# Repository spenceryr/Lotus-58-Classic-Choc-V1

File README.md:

### Notice! Project files in the development branches are NOT intended for public use in production of PCB's, may or may not be tested and may change or be removed without notice! 
If you order PCB's from these, YOU bear the sole responsibility for how these turn out!!! Please use the Gerber files for producing PCB's, found under the header 'Releases' instead (Look here >>). Also please note the difference between a 'Pre-release' (partially/fully untested, basically what I order a prototype PCB from to test) and a full actual 'Release' which is fully tested, built and ready to be used to produce PCB's.

# Lotus 58 Glow - Classic
#### Lotus 58 Classic is the wired designs of the Lotus keyboard. Wireless with BLE and 2.4Ghz dongled wireless reside in other repositories.

Starting with simple tweaks to the Lily58 Glow before ordering a set of PCB's it quickly spiraled out of control, and I ended up with what wasn't quite a Lily58 anymore, and although very similar in layout, it is no longer compatible with plate and case design. 

Because of this, it was renamed Lotus58, referencing another flower much like the lily in the name Lily58.

(photo from reddit by u/bduzik)

## General Specifications

- Layout very similar to the original Lily58 family
- Per key RGB and RGB underglow
- Kaihl Hot-swap sockets for MX compatible switches
- Can be used as a standalone Gamepad for either hand
- Optional 0.91" OLED Screens and rotary encoders (one each per side)
- All components through-hole and easily soldered for beginners (SMD option for diodes)
- Designed with a sandwich-style plate/case as part of the design

## Layout variations

- Optional plate layout with OLED screen (Encoder can be placed on upper thumb key position)
- Optional plate layout with rotary encoder (Removes OLED screen for that side)  
- Optional plate layout with no hole for OLED or upper encoder (Encoder can be placed on upper thumb key position)

## 3D-printed Cases
**There are a couple of 'official' commissioned designs for 3D printed cases for the Lotus 58 Glow, available in a separate Git [here](https://github.com/TweetyDaBird/Lotus-Cases).** 

And you can find several more made by users using Google, and/or by joining the Discord channel and chatting to the builders/designers and users.

## Things to note when ordering PCB's
### Finding the Gerber files
If you are not aiming at modifying things, don't look for the gerber files in the folders, pretty please!</BR>
And please don't open yet another issue about it! </BR>
The gerber files are where they belong, zipped up in releases, look under that header for the version you want.

### Tips & Tricks
- Most PCB manufacturers have a MOQ of 5 PCB's, meaning you end up with 2½ keyboards when finished.
- The recommended PCB thickness is 1.6 mm, both for the main PCB and plates to allow the keyswitches to grip the plate and lock in place securely.

If ordering from [JLCPCB](https://www.jlcpcb.com) the plate Gerber files include a reference putting the added serial etc on a breakaway part for a clean look with minimal cost, if using another manufacturer it's possible they have additional fee's for removing the extra text, or you should consider plotting the Gerber files yourself with the correct reference for your manufacturer. Otherwise use the standard settings from JLPCB.

## Build guide
**Some basic build instructions are in the [WIKI](https://github.com/TweetyDaBird/Lotus-58-Classic/wiki), and I really try to keep these updated.** But please keep in mind that whenever these instructions conflict with information on the PCB silkscreen, the silkscreen is and always will be the correct source of information! It's always updated with the version, and the most current information for the PCB version in question. 

**The intent has always been that the keyboard should be able to be fully built with some very basic soldering skills and the instructions on the silkscreen.**

### Discord for further build help and discussions!

## Buy a kit!
I sell complete kits, making it easy to build your keyboard, and it also supports prototypes for new wacky ones.

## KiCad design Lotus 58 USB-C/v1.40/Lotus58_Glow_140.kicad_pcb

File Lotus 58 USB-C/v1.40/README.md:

# Lotus 58 v1.40

Starting with simple tweaks to the Lily58 Glow before ordering a set of PCB's it quickly spiraled out of control, and I ended up with what wasn't quite a Lily58 anymore, and although very similar in layout, it is no longer compatible with plate and case design. 

Because of this, it was renamed Lotus58, referencing another flower much like the lily in the name Lily58.

# Lotus 58 Glow

(photo from reddit by u/bduzik)

Fully compatabile with v1.11, physically identical outline for plates etc. and identical Firmware.

# Parts needed

| Name of part | Qty. | Optional | Remarks | Aliexpress |
| ------------ | ---- | -------- | ------- | --------------- |
| PCB          | 2    | X        | 1,6mm thick | X           |
| Top plate         | 2 | X        | Optional layouts for OLED or encoder in top position. | X |
| Bottom plate         | 2 | X        | X | X |
| Kailh hotswap socket | 56-58 | X | Qty. depends on layout. | [link](https://www.aliexpress.com/item/-/4001051840976.html?spm=a2g0s.8937460.0.0.6f132e0eKYB5RQ&_ga=2.174414626.1036705865.1612730332-979734211.1611132916&_gac=1.119713146.1611132916.CjwKCAiAxp-ABhALEiwAXm6IyZF-HtTdP3MQioG5GOxLvsaJfBbhqTGIQbmV0LXKDx2MZSDJJJTbaBoCPkoQAvD_BwE) |
| Diodes 1N4841 (TH) or 1N4148W (SMD) | 56-58 | X | Qty. depends on layout. TH recommended for beginners. | [link(TH)](https://www.aliexpress.com/item/HOT-SELL-100-PCS-1N4148-DO-35-IN4148-Silicon-Switching-Diode-FREE-SHIPPMENT/32660088529.html?spm=a2g0s.8937460.0.0.c1b82e0edjrOT3&_ga=2.216963734.1036705865.1612730332-979734211.1611132916&_gac=1.53192282.1611132916.CjwKCAiAxp-ABhALEiwAXm6IyZF-HtTdP3MQioG5GOxLvsaJfBbhqTGIQbmV0LXKDx2MZSDJJJTbaBoCPkoQAvD_BwE) or [link(SMD)](https://www.aliexpress.ru/item/-/1005002059571417.html?spm=a2g0s.8937460.0.0.c1b82e0edjrOT3&_ga=2.216963734.1036705865.1612730332-979734211.1611132916&_gac=1.53192282.1611132916.CjwKCAiAxp-ABhALEiwAXm6IyZF-HtTdP3MQioG5GOxLvsaJfBbhqTGIQbmV0LXKDx2MZSDJJJTbaBoCPkoQAvD_BwE) |
| Capacitors 100 nF | 0-4 | ✔ | Qty. depends on layout. 2 needed for each encoder installed. | [link](https://www.aliexpress.com/item/-/32971478818.html?spm=a2g0s.8937460.0.0.6f132e0eKYB5RQ&_ga=2.149198518.1036705865.1612730332-979734211.1611132916&_gac=1.48473428.1611132916.CjwKCAiAxp-ABhALEiwAXm6IyZF-HtTdP3MQioG5GOxLvsaJfBbhqTGIQbmV0LXKDx2MZSDJJJTbaBoCPkoQAvD_BwE) |
| 0.91" OLED Display | 0-2 | ✔ | Qty. depends on layout. | [link](https://www.aliexpress.com/item/-/4001028384269.html?spm=a2g0s.8937460.0.0.c1b82e0edjrOT3&_ga=2.241041155.1036705865.1612730332-979734211.1611132916&_gac=1.219449963.1611132916.CjwKCAiAxp-ABhALEiwAXm6IyZF-HtTdP3MQioG5GOxLvsaJfBbhqTGIQbmV0LXKDx2MZSDJJJTbaBoCPkoQAvD_BwE) |
| USB C Connector | 2 | X | X | [link](https://www.lcsc.com/product-detail/USB-Connectors_G-Switch-GT-USB-7014C_C963373.html) |
| SRV05-4	ESD | 2 | X | ESD protection for USB link. | [link](https://www.lcsc.com/product-detail/Electrostatic-and-Surge-Protection-TVS-ESD_TECH-PUBLIC-SRV05-4_C558418.html)|
| Ferrite bead | 4 | X | ESD protection for USB link. | [link](https://www.lcsc.com/product-detail/Ferrite-Beads_Murata-Electronics-BLM18SG700TZ1D_C882974.html) |
| M2 * 10 mm standoff | 10 | X | Rounded, max 3.7 mm in diameter | [link](https://www.aliexpress.com/item/-/32863484622.html?spm=a2g0s.8937460.0.0.c1b82e0edjrOT3&_ga=2.215809815.1036705865.1612730332-979734211.1611132916&_gac=1.26395343.1611132916.CjwKCAiAxp-ABhALEiwAXm6IyZF-HtTdP3MQioG5GOxLvsaJfBbhqTGIQbmV0LXKDx2MZSDJJJTbaBoCPkoQAvD_BwE) |
| M2 * 4 mm screw | 20 | X | 4-8 mm length fits, low profile hex head recommended | [link](https://www.aliexpress.com/item/-/32966917947.html?spm=a2g0s.8937460.0.0.c1b82e0edjrOT3&_ga=2.246923140.1036705865.1612730332-979734211.1611132916&_gac=1.263439230.1611132916.CjwKCAiAxp-ABhALEiwAXm6IyZF-HtTdP3MQioG5GOxLvsaJfBbhqTGIQbmV0LXKDx2MZSDJJJTbaBoCPkoQAvD_BwE) |
| Silicon pads | 10 | X | X | [link](https://www.aliexpress.com/item/-/32912066603.html?spm=a2g0s.8937460.0.0.6f132e0eKYB5RQ&_ga=2.145547188.1036705865.1612730332-979734211.1611132916&_gac=1.57255896.1611132916.CjwKCAiAxp-ABhALEiwAXm6IyZF-HtTdP3MQioG5GOxLvsaJfBbhqTGIQbmV0LXKDx2MZSDJJJTbaBoCPkoQAvD_BwE) |
| Pro Micro | 2 | X | Can be built with various ProMicro clones as well as Elite C (Or nice!nano for a wireless keyboard) | [link](https://www.aliexpress.com/item/-/32849563958.html?spm=a2g0s.8937460.0.0.c1b82e0edjrOT3&_ga=2.175422242.1036705865.1612730332-979734211.1611132916&_gac=1.225165928.1611132916.CjwKCAiAxp-ABhALEiwAXm6IyZF-HtTdP3MQioG5GOxLvsaJfBbhqTGIQbmV0LXKDx2MZSDJJJTbaBoCPkoQAvD_BwE) |
| MillMax low profile sockets | 1 | ✔ | Purchased as 1x64 pin and split | [link](https://eu.mouser.com/ProductDetail/575-641503)|
| Rotary Encoder | 0-2 | ✔ | Qty. depends on layout. | [link](https://www.aliexpress.com/item/10000056483250.html?spm=a2g0o.productlist.0.0.64951c5fKcPiug&algo_pvid=b530d9b1-fbd2-4598-bf53-bece1343826f&algo_expid=b530d9b1-fbd2-4598-bf53-bece1343826f-2&btsid=2100bdd016135510210168102eefcc&ws_ab_test=searchweb0_0,searchweb201602_,searchweb201603_) |
| Rotary Encoder Knob | 0-2 | ✔ | One needed for each encoder. Clearance for max 24 mm diameter, pick halfshaft or spline according to encoder choice.  | [link](https://www.aliexpress.com/item/10000056483250.html?spm=a2g0o.productlist.0.0.64951c5fKcPiug&algo_pvid=b530d9b1-fbd2-4598-bf53-bece1343826f&algo_expid=b530d9b1-fbd2-4598-bf53-bece1343826f-2&btsid=2100bdd016135510210168102eefcc&ws_ab_test=searchweb0_0,searchweb201602_,searchweb201603_) |
| SK6803/SK6805/SK6812 mini-E (3535) | 12/58 (70) | ✔ | Qty. depends on layout and if used as per-key or underglow (or both). Mini E are winged for easier soldering.| [link](https://www.aliexpress.com/item/4000475685852.html?spm=a2g0o.productlist.0.0.3ec76d0aSbZSMy&algo_pvid=c175ec6d-d797-4bad-885d-dd7ab2025889&algo_expid=c175ec6d-d797-4bad-885d-dd7ab2025889-1&btsid=0b0a01f816148497094017930e33f7&ws_ab_test=searchweb0_0,searchweb201602_,searchweb201603_) |
| MSK12C02 Slide switch | 0-2 | ✔ | Optional RGB select or Power switch | [link](https://www.lcsc.com/product-detail/Slide-Switches_SHOU-HAN-MSK12C02_C431540.html)|

## Things to note when ordering PCB's
### Finding the Gerber files
If you are not aiming at modifying things, don't look for the gerber files in the folders, pretty please!</BR>
And please don't open yet another issue about it! </BR>
The gerber files are where they belong, zipped up in releases, look under that header for the version you want.

### Tips & Tricks
- Most PCB manufacturers have a MOQ of 5 PCB's, meaning you end up with 2½ keyboards when finished.
- The recommended PCB thickness is 1.6 mm, both for the main PCB and plates to allow the keyswitches to grip the plate and lock in place securely.

If ordering from [JLPCB](https://www.jlpcb.com) the plate Gerber files include a reference putting the added serial etc on a breakaway part for a clean look with minimal cost, if using another manufacturer it's possible they have additional fee's for removing the extra text, or you should consider plotting the Gerber files yourself with the correct reference for your manufacturer. Otherwise use the standard settings from JLPCB.

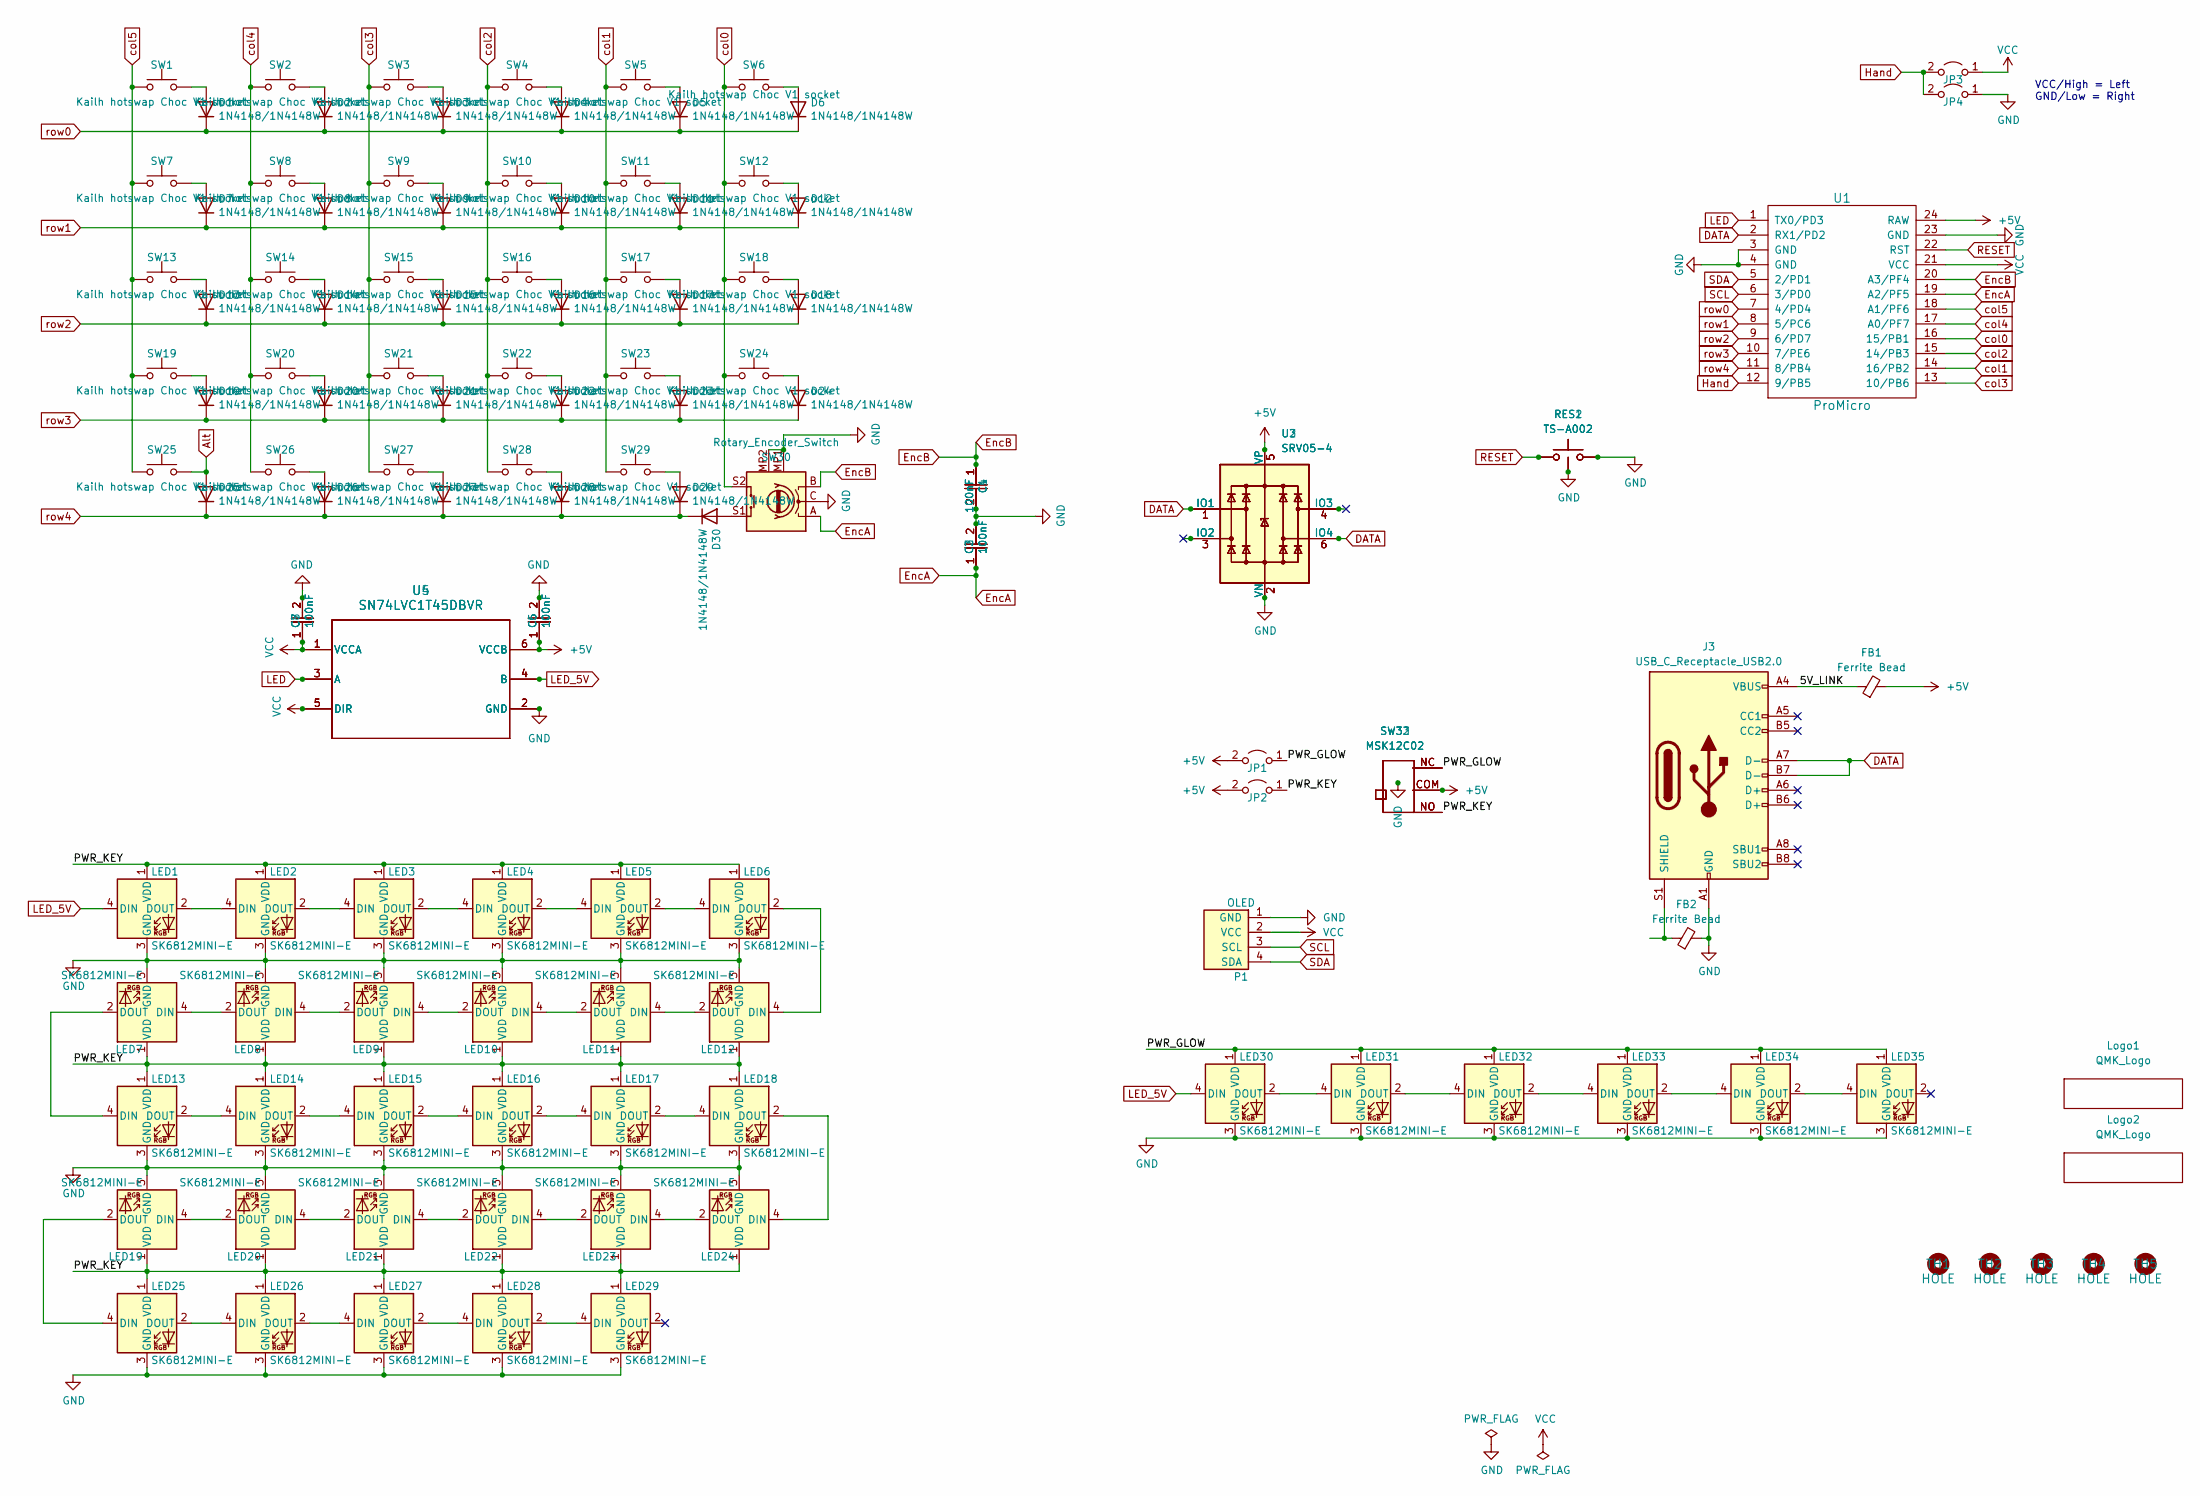
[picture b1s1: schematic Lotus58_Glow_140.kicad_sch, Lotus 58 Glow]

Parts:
C1, C2, C3, C4, C5, C6, C7, C8: 100nF; CAP_CL05_SAM
D1, D2, D3, D4, D5, D6, D7, D8, D9, D10, D11, D12, D13, D14, D15, D16, D17, D18, D19, D20, D21, D22, D23, D24, D25, D26, D27, D28, D29, D30: 1N4148/1N4148W; Diode_DO35_SOD123
FB1, FB2: Ferrite Bead; C_0603_1608Metric_Pad1.08x0.95mm_HandSolder; LCSC C882974
J3: USB_C_Receptacle_USB2.0; Molex-216990_GCT-USB45xx_HRO-TYPE-C-31-M-13x-PiMicro; LCSC C963373
JP1, JP2, JP3: LEFT; Jumper_min_v2
JP4: RIGHT; Jumper_min_v2
LED1, LED2, LED3, LED4, LED5, LED6, LED7, LED8, LED9, LED10, LED11, LED12, LED13, LED14, LED15, LED16, LED17, LED18, LED19, LED20, LED21, LED22, LED23, LED24, LED25, LED26, LED27, LED28, LED29, LED30, LED31, LED32, LED33, LED34, LED35: SK6812MINI-E; MX_SK6812MINI-E_REVERSIBLE
Logo1, Logo2: QMK_Logo; qmk logo
P1: OLED; SSD1306-0.91-OLED-4pin-128x32 doublesided
RES1, RES2: TS-A002; YTS-A002; LCSC C2888934
SW1, SW2, SW3, SW4, SW5, SW6, SW7, SW8, SW9, SW10, SW11, SW12, SW13, SW14, SW15, SW16, SW17, SW18, SW19, SW20, SW21, SW22, SW23, SW24, SW25, SW26, SW27, SW28, SW29: Kailh hotswap Choc V1 socket; SW_Kailh_Choc_V1_HotSwap_Reversible
SW30: Rotary_Encoder_Switch; Encoder_Alps_EC11E_Small
SW32, SW33: MSK12C02
TH1, TH2, TH3, TH4, TH5: HOLE; Spacer PCB hole
U1: ProMicro; ProMicro_jumpers_V2
U2, U3: SRV05-4; SOT-23-6; LCSC C558418
U4, U5: SN74LVC1T45DBVR; DBV0006A_N

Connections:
+5V: C5.1, C6.1, FB1.2, JP1.2 (B), JP2.2 (B), SW32.COM, SW33.COM, U1.24 (RAW), U2.5 (VP), U3.5 (VP), U4.6 (VCCB), U5.6 (VCCB)
/5V_LINK: FB1.1, J3.A4 (VBUS), J3.A9 (VBUS), J3.B4 (VBUS), J3.B9 (VBUS)
/PWR_GLOW: JP1.1 (A), LED30.1 (VDD), LED31.1 (VDD), LED32.1 (VDD), LED33.1 (VDD), LED34.1 (VDD), LED35.1 (VDD), SW32.NC, SW33.NC
/PWR_KEY: JP2.1 (A), LED1.1 (VDD), LED2.1 (VDD), LED3.1 (VDD), LED4.1 (VDD), LED5.1 (VDD), LED6.1 (VDD), LED7.1 (VDD), LED8.1 (VDD), LED9.1 (VDD), LED10.1 (VDD), LED11.1 (VDD), LED12.1 (VDD), LED13.1 (VDD), LED14.1 (VDD), LED15.1 (VDD), LED16.1 (VDD), LED17.1 (VDD), LED18.1 (VDD), LED19.1 (VDD), LED20.1 (VDD), LED21.1 (VDD), LED22.1 (VDD), LED23.1 (VDD), LED24.1 (VDD), LED25.1 (VDD), LED26.1 (VDD), LED27.1 (VDD), LED28.1 (VDD), LED29.1 (VDD), SW32.NO, SW33.NO
Alt: D25.2 (A), SW25.1
DATA: J3.A7 (D-), J3.B7 (D-), U1.2 (RX1/PD2), U2.1 (IO1), U2.6 (IO4), U3.1 (IO1), U3.6 (IO4)
EncA: C2.1, C3.1, SW30.A, U1.19 (A2/PF5)
EncB: C1.1, C4.1, SW30.B, U1.20 (A3/PF4)
GND: C1.2, C2.2, C3.2, C4.2, C5.2, C6.2, C7.2, C8.2, FB2.2, J3.A1 (GND), J3.A12 (GND), J3.B1 (GND), J3.B12 (GND), JP4.1 (A), LED1.3 (GND), LED2.3 (GND), LED3.3 (GND), LED4.3 (GND), LED5.3 (GND), LED6.3 (GND), LED7.3 (GND), LED8.3 (GND), LED9.3 (GND), LED10.3 (GND), LED11.3 (GND), LED12.3 (GND), LED13.3 (GND), LED14.3 (GND), LED15.3 (GND), LED16.3 (GND), LED17.3 (GND), LED18.3 (GND), LED19.3 (GND), LED20.3 (GND), LED21.3 (GND), LED22.3 (GND), LED23.3 (GND), LED24.3 (GND), LED25.3 (GND), LED26.3 (GND), LED27.3 (GND), LED28.3 (GND), LED29.3 (GND), LED30.3 (GND), LED31.3 (GND), LED32.3 (GND), LED33.3 (GND), LED34.3 (GND), LED35.3 (GND), P1.1 (GND), RES1.2, RES1.3, RES2.2, RES2.3, SW30.C, SW30.MP1 (GND), SW30.MP2 (GND), SW32.MP (GND), SW33.MP (GND), U1.3 (GND), U1.4 (GND), U1.23 (GND), U2.2 (VN), U3.2 (VN), U4.2 (GND), U5.2 (GND)
Hand: JP3.2 (B), JP4.2 (B), U1.12 (9/PB5)
LED: U1.1 (TX0/PD3), U4.3 (A), U5.3 (A)
LED_5V: LED1.4 (DIN), LED30.4 (DIN), U4.4 (B), U5.4 (B)
unnamed: D1.2 (A), SW1.1
unnamed: D2.2 (A), SW2.1
unnamed: D3.2 (A), SW3.1
unnamed: D4.2 (A), SW4.1
unnamed: D5.2 (A), SW5.1
unnamed: D6.2 (A), SW6.1
unnamed: D7.2 (A), SW7.1
unnamed: D8.2 (A), SW8.1
unnamed: D9.2 (A), SW9.1
unnamed: D10.2 (A), SW10.1
unnamed: D11.2 (A), SW11.1
unnamed: D12.2 (A), SW12.1
unnamed: D13.2 (A), SW13.1
unnamed: D14.2 (A), SW14.1
unnamed: D15.2 (A), SW15.1
unnamed: D16.2 (A), SW16.1
unnamed: D17.2 (A), SW17.1
unnamed: D18.2 (A), SW18.1
unnamed: D19.2 (A), SW19.1
unnamed: D20.2 (A), SW20.1
unnamed: D21.2 (A), SW21.1
unnamed: D22.2 (A), SW22.1
unnamed: D23.2 (A), SW23.1
unnamed: D24.2 (A), SW24.1
unnamed: D26.2 (A), SW26.1
unnamed: D27.2 (A), SW27.1
unnamed: D28.2 (A), SW28.1
unnamed: D29.2 (A), SW29.1
unnamed: D30.2 (A), SW30.S1
unnamed: FB2.1, J3.S1 (SHIELD)
unnamed: LED1.2 (DOUT), LED2.4 (DIN)
unnamed: LED2.2 (DOUT), LED3.4 (DIN)
unnamed: LED3.2 (DOUT), LED4.4 (DIN)
unnamed: LED4.2 (DOUT), LED5.4 (DIN)
unnamed: LED5.2 (DOUT), LED6.4 (DIN)
unnamed: LED7.4 (DIN), LED8.2 (DOUT)
unnamed: LED8.4 (DIN), LED9.2 (DOUT)
unnamed: LED10.4 (DIN), LED11.2 (DOUT)
unnamed: LED9.4 (DIN), LED10.2 (DOUT)
unnamed: LED11.4 (DIN), LED12.2 (DOUT)
unnamed: LED6.2 (DOUT), LED12.4 (DIN)
unnamed: LED7.2 (DOUT), LED13.4 (DIN)
unnamed: LED13.2 (DOUT), LED14.4 (DIN)
unnamed: LED14.2 (DOUT), LED15.4 (DIN)
unnamed: LED15.2 (DOUT), LED16.4 (DIN)
unnamed: LED16.2 (DOUT), LED17.4 (DIN)
unnamed: LED17.2 (DOUT), LED18.4 (DIN)
unnamed: LED18.2 (DOUT), LED24.4 (DIN)
unnamed: LED19.4 (DIN), LED20.2 (DOUT)
unnamed: LED19.2 (DOUT), LED25.4 (DIN)
unnamed: LED20.4 (DIN), LED21.2 (DOUT)
unnamed: LED21.4 (DIN), LED22.2 (DOUT)
unnamed: LED22.4 (DIN), LED23.2 (DOUT)
unnamed: LED23.4 (DIN), LED24.2 (DOUT)
unnamed: LED25.2 (DOUT), LED26.4 (DIN)
unnamed: LED26.2 (DOUT), LED27.4 (DIN)
unnamed: LED27.2 (DOUT), LED28.4 (DIN)
unnamed: LED28.2 (DOUT), LED29.4 (DIN)
unnamed: LED30.2 (DOUT), LED31.4 (DIN)
unnamed: LED31.2 (DOUT), LED32.4 (DIN)
unnamed: LED32.2 (DOUT), LED33.4 (DIN)
unnamed: LED33.2 (DOUT), LED34.4 (DIN)
unnamed: LED34.2 (DOUT), LED35.4 (DIN)
RESET: RES1.1, RES2.1, U1.22 (RST)
SCL: P1.3 (SCL), U1.6 (3/PD0)
SDA: P1.4 (SDA), U1.5 (2/PD1)
VCC: C7.1, C8.1, JP3.1 (A), P1.2 (VCC), U1.21 (VCC), U4.1 (VCCA), U4.5 (DIR), U5.1 (VCCA), U5.5 (DIR)
col0: SW6.2, SW12.2, SW18.2, SW24.2, SW30.S2, U1.16 (15/PB1)
col1: SW5.2, SW11.2, SW17.2, SW23.2, SW29.2, U1.14 (16/PB2)
col2: SW4.2, SW10.2, SW16.2, SW22.2, SW28.2, U1.15 (14/PB3)
col3: SW3.2, SW9.2, SW15.2, SW21.2, SW27.2, U1.13 (10/PB6)
col4: SW2.2, SW8.2, SW14.2, SW20.2, SW26.2, U1.17 (A0/PF7)
col5: SW1.2, SW7.2, SW13.2, SW19.2, SW25.2, U1.18 (A1/PF6)
row0: D1.1 (K), D2.1 (K), D3.1 (K), D4.1 (K), D5.1 (K), D6.1 (K), U1.7 (4/PD4)
row1: D7.1 (K), D8.1 (K), D9.1 (K), D10.1 (K), D11.1 (K), D12.1 (K), U1.8 (5/PC6)
row2: D13.1 (K), D14.1 (K), D15.1 (K), D16.1 (K), D17.1 (K), D18.1 (K), U1.9 (6/PD7)
row3: D19.1 (K), D20.1 (K), D21.1 (K), D22.1 (K), D23.1 (K), D24.1 (K), U1.10 (7/PE6)
row4: D25.1 (K), D26.1 (K), D27.1 (K), D28.1 (K), D29.1 (K), D30.1 (K), U1.11 (8/PB4)

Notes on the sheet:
VCC/High = Left GND/Low = Right

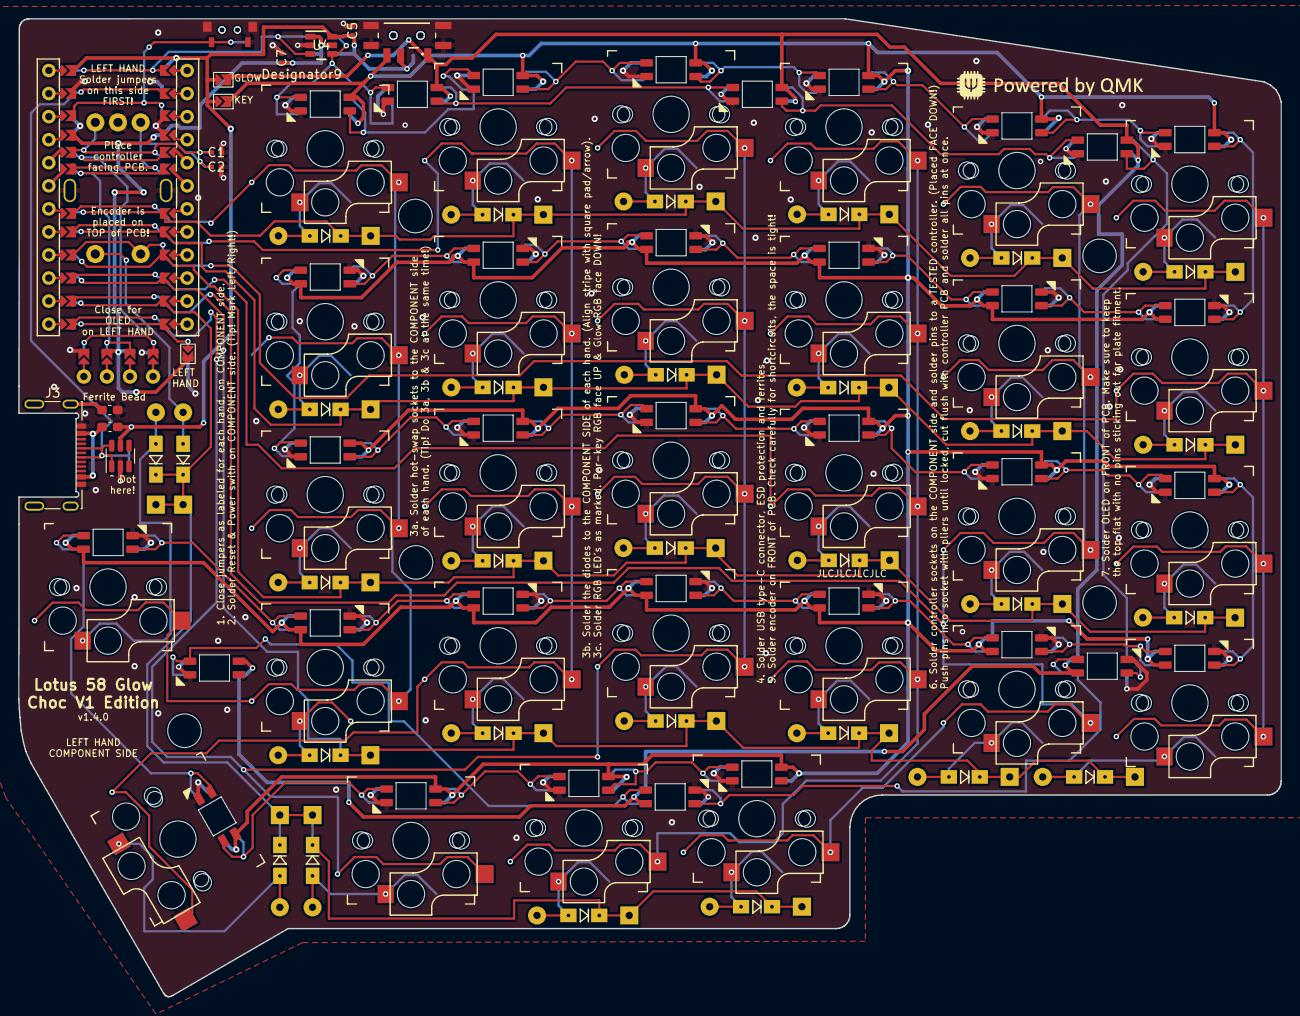
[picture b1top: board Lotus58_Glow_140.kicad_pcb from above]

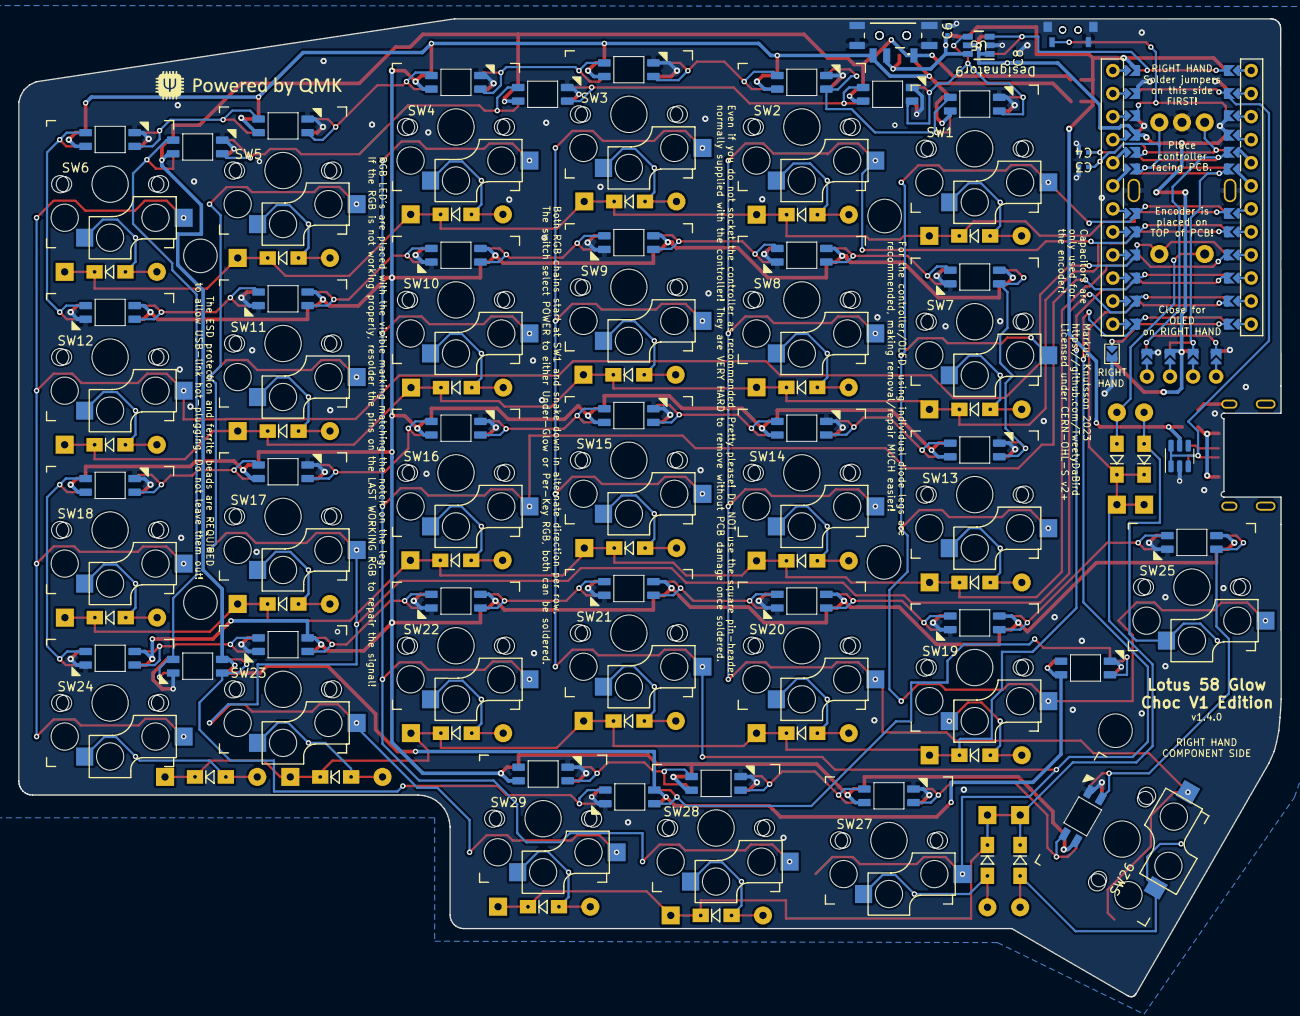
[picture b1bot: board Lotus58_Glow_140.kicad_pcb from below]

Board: 2 copper layers, 139.1 x 107.7 mm, 127 parts (41 on the bottom side), 90 nets.

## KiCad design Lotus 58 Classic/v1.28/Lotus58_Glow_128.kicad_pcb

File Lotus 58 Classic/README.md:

# Lotus 58 Glow

Starting with simple tweaks to the Lily58 Glow before ordering a set of PCB's it quickly spiraled out of control, and I ended up with what wasn't quite a Lily58 anymore, and although very similar in layout, it is no longer compatible with plate and case design. 

Because of this, it was renamed Lotus58, referencing another flower much like the lily in the name Lily58.

(photo from reddit by u/bduzik)

## TRRS link version - Lotus 58 Classic

This is the original branch of the Lotus 58 Glow design, using the TRRS link. A lot of features have been added along the way for the newer versions.

## General Specifications

- Layout very similar to the original Lily58 family
- Per key RGB and RGB underglow
- Kaihl Hot-swap sockets for MX compatible switches
- Can be used as a standalone Gamepad for either hand
- Optional 0.91" OLED Screens and rotary encoders (one each per side)
- All components through-hole and easily soldered for beginners (SMD option for diodes)
- Designed with a sandwich-style plate/case as part of the design

## Layout variations

- Optional plate layout with OLED screen (Encoder can be placed on upper thumb key position)
- Optional plate layout with rotary encoder (Removes OLED screen for that side)  
- Optional plate layout with no hole for OLED or upper encoder (Encoder can be placed on upper thumb key position)

## Things to note when ordering PCB's
### Finding the Gerber files
If you are not aiming at modifying things, don't look for the gerber files in the folders, pretty please!</BR>
And please don't open yet another issue about it! </BR>
The gerber files are where they belong, zipped up in releases, look under that header for the version you want.

### Tips & Tricks
- Most PCB manufacturers have a MOQ of 5 PCB's, meaning you end up with 2½ keyboards when finished.
- The recommended PCB thickness is 1.6 mm, both for the main PCB and plates to allow the keyswitches to grip the plate and lock in place securely.

If ordering from [JLCPCB](https://www.jlcpcb.com) the plate Gerber files include a reference putting the added serial etc on a breakaway part for a clean look with minimal cost, if using another manufacturer it's possible they have additional fee's for removing the extra text, or you should consider plotting the Gerber files yourself with the correct reference for your manufacturer. Otherwise use the standard settings from JLPCB.

## Build guide
**Some basic build instructions are in the [WIKI](https://github.com/TweetyDaBird/Lotus-58-Classic/wiki), and I really try to keep these updated.** But please keep in mind that whenever these instructions conflict with information on the PCB silkscreen, the silkscreen is and always will be the correct source of information! It's always updated with the version, and the most current information for the PCB version in question. 

**The intent has always been that the keyboard should be able to be fully built with some very basic soldering skills and the instructions on the silkscreen.**

### Discord for further build help and discussions!

## Buy a kit!
I sell complete kits, making it easy to build your keyboard, and it also supports prototypes for new wacky ones.

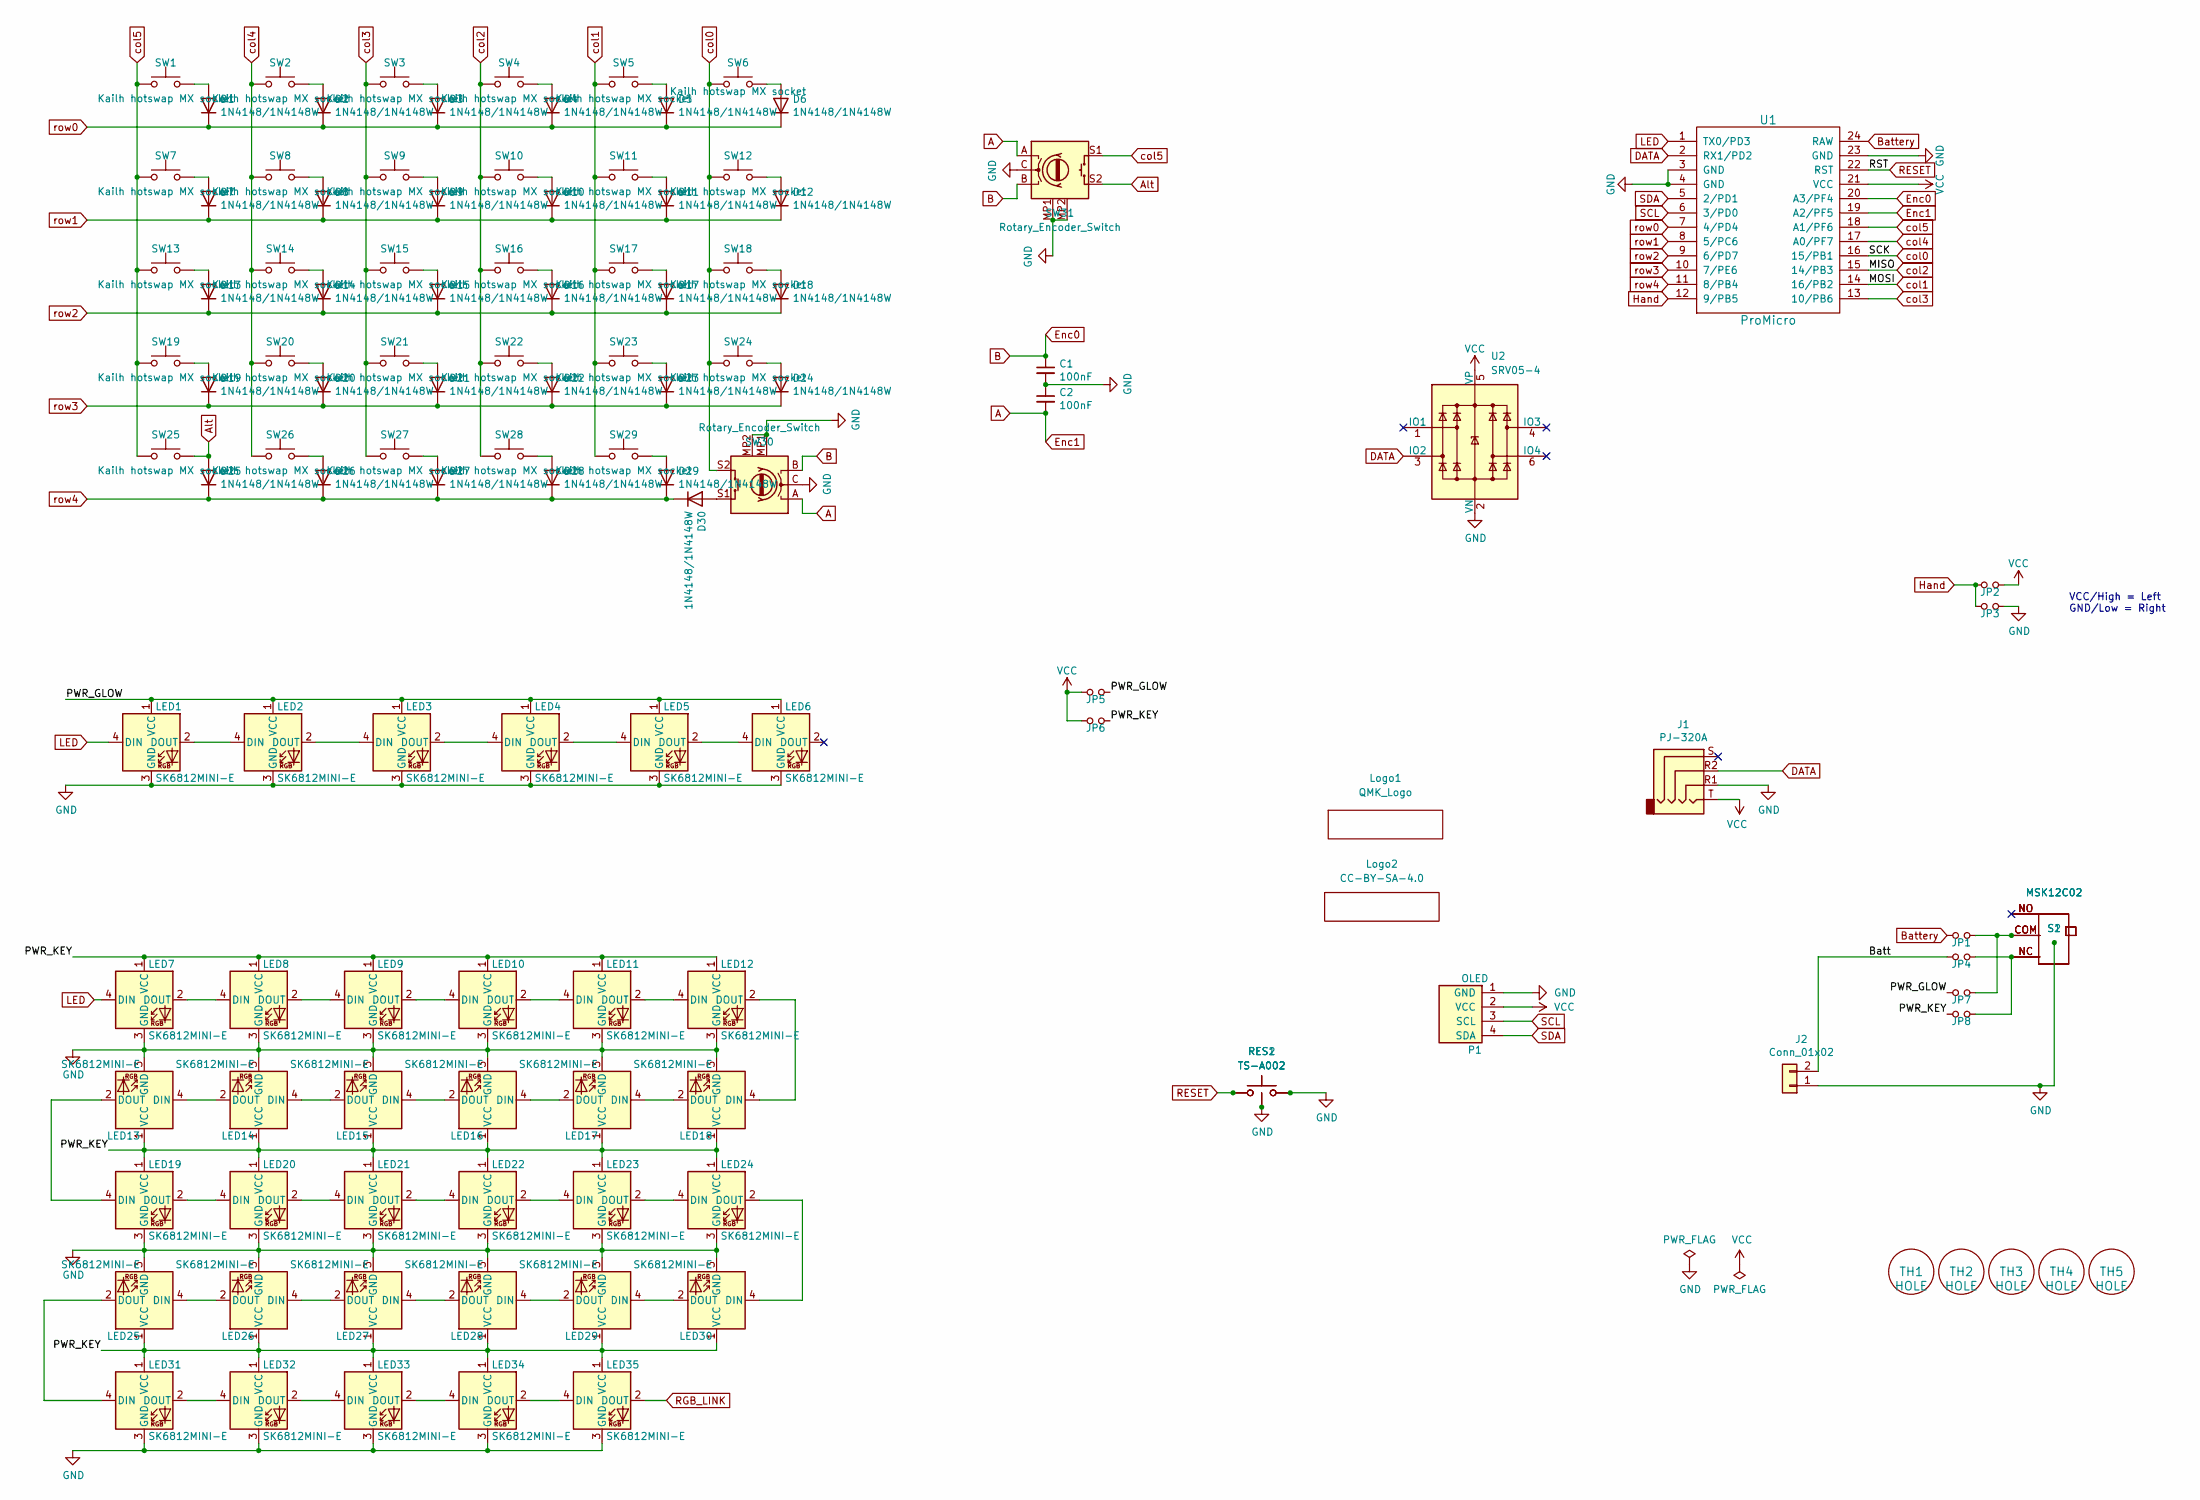
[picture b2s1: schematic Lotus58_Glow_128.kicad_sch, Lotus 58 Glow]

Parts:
C1, C2: 100nF; RESISTOR_Reversible
D1, D2, D3, D4, D5, D6, D7, D8, D9, D10, D11, D12, D13, D14, D15, D16, D17, D18, D19, D20, D21, D22, D23, D24, D25, D26, D27, D28, D29, D30: 1N4148/1N4148W; Diode_DO35_SOD123
J1: PJ-320A; MJ-4PP-9_alim
J2: Conn_01x02; PinHeader_1x02_P2.54mm_Vertical
JP1, JP4, JP5, JP6, JP7, JP8: FULL; Jumper_min_v2
JP2: LEFT; Jumper_min_v2
JP3: RIGHT; Jumper_min_v2
LED1, LED2, LED3, LED4, LED5, LED6, LED7, LED8, LED9, LED10, LED11, LED12, LED13, LED14, LED15, LED16, LED17, LED18, LED19, LED20, LED21, LED22, LED23, LED24, LED25, LED26, LED27, LED28, LED29, LED30, LED31, LED32, LED33, LED34, LED35: SK6812MINI-E; MX_SK6812MINI-E_REVERSIBLE
Logo1: QMK_Logo; qmk logo
Logo2: CC-BY-SA-4.0; CC_BY_SA_40_line
P1: OLED; SSD1306-0.91-OLED-4pin-128x32 doublesided
RES1, RES2: TS-A002; YTS-A002; LCSC C2888934
S1, S2: MSK12C02; Manufacturer_Part_Number MSK12C02
SW1, SW2, SW3, SW4, SW5, SW6, SW7, SW8, SW9, SW10, SW11, SW12, SW13, SW14, SW15, SW16, SW17, SW18, SW19, SW20, SW21, SW22, SW23, SW24, SW25, SW26, SW27, SW28, SW29: Kailh hotswap MX socket; Kailh_socket_MX_reversible_RGB
SW30: Rotary_Encoder_Switch; RotaryEncoder_Alps_EC11E-Switch_Vertical_H20_special
SW31: Rotary_Encoder_Switch; RotaryEncoder_Alps_EC11E-Switch_Special
TH1, TH2, TH3, TH4, TH5: HOLE; Spacer PCB hole
U1: ProMicro; ProMicro_Reversible_orig
U2: SRV05-4; SOT-23-6

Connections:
/Batt: J2.2, JP4.1
/PWR_GLOW: JP5.2, JP7.1, LED1.1 (VCC), LED2.1 (VCC), LED3.1 (VCC), LED4.1 (VCC), LED5.1 (VCC), LED6.1 (VCC)
/PWR_KEY: JP6.2, JP8.1, LED7.1 (VCC), LED8.1 (VCC), LED9.1 (VCC), LED10.1 (VCC), LED11.1 (VCC), LED12.1 (VCC), LED13.1 (VCC), LED14.1 (VCC), LED15.1 (VCC), LED16.1 (VCC), LED17.1 (VCC), LED18.1 (VCC), LED19.1 (VCC), LED20.1 (VCC), LED21.1 (VCC), LED22.1 (VCC), LED23.1 (VCC), LED24.1 (VCC), LED25.1 (VCC), LED26.1 (VCC), LED27.1 (VCC), LED28.1 (VCC), LED29.1 (VCC), LED30.1 (VCC), LED31.1 (VCC), LED32.1 (VCC), LED33.1 (VCC), LED34.1 (VCC), LED35.1 (VCC)
A: C2.2, SW30.A, SW31.A, U1.19 (A2/PF5)
Alt: D25.2 (A), SW25.2, SW31.S2
B: C1.1, SW30.B, SW31.B, U1.20 (A3/PF4)
Battery: JP1.1, U1.24 (RAW)
DATA: J1.R2, U1.2 (RX1/PD2), U2.3 (IO2)
GND: C1.2, C2.1, J1.R1, J2.1, JP3.1, LED1.3 (GND), LED2.3 (GND), LED3.3 (GND), LED4.3 (GND), LED5.3 (GND), LED6.3 (GND), LED7.3 (GND), LED8.3 (GND), LED9.3 (GND), LED10.3 (GND), LED11.3 (GND), LED12.3 (GND), LED13.3 (GND), LED14.3 (GND), LED15.3 (GND), LED16.3 (GND), LED17.3 (GND), LED18.3 (GND), LED19.3 (GND), LED20.3 (GND), LED21.3 (GND), LED22.3 (GND), LED23.3 (GND), LED24.3 (GND), LED25.3 (GND), LED26.3 (GND), LED27.3 (GND), LED28.3 (GND), LED29.3 (GND), LED30.3 (GND), LED31.3 (GND), LED32.3 (GND), LED33.3 (GND), LED34.3 (GND), LED35.3 (GND), P1.1 (GND), RES1.2, RES1.3, RES2.2, RES2.3, S1.MP (GND), S2.MP (GND), SW30.C, SW30.MP1 (GND), SW30.MP2 (GND), SW31.C, SW31.MP1 (GND), SW31.MP2 (GND), U1.3 (GND), U1.4 (GND), U1.23 (GND), U2.2 (VN)
Hand: JP2.2, JP3.2, U1.12 (9/PB5)
LED: LED1.4 (DIN), LED7.4 (DIN), U1.1 (TX0/PD3)
unnamed: D2.2 (A), SW2.2
unnamed: D3.2 (A), SW3.2
unnamed: D4.2 (A), SW4.2
unnamed: D5.2 (A), SW5.2
unnamed: D6.2 (A), SW6.2
unnamed: D7.2 (A), SW7.2
unnamed: D8.2 (A), SW8.2
unnamed: D9.2 (A), SW9.2
unnamed: D10.2 (A), SW10.2
unnamed: D11.2 (A), SW11.2
unnamed: D12.2 (A), SW12.2
unnamed: D13.2 (A), SW13.2
unnamed: D14.2 (A), SW14.2
unnamed: D15.2 (A), SW15.2
unnamed: D16.2 (A), SW16.2
unnamed: D17.2 (A), SW17.2
unnamed: D18.2 (A), SW18.2
unnamed: D19.2 (A), SW19.2
unnamed: D20.2 (A), SW20.2
unnamed: D21.2 (A), SW21.2
unnamed: D22.2 (A), SW22.2
unnamed: D23.2 (A), SW23.2
unnamed: D24.2 (A), SW24.2
unnamed: D26.2 (A), SW26.2
unnamed: D27.2 (A), SW27.2
unnamed: D28.2 (A), SW28.2
unnamed: D29.2 (A), SW29.2
unnamed: D30.2 (A), SW30.S1
unnamed: JP1.2, JP7.2, S1.COM, S2.COM
unnamed: JP4.2, JP8.2, S1.NC, S2.NC
unnamed: LED1.2 (DOUT), LED2.4 (DIN)
unnamed: LED2.2 (DOUT), LED3.4 (DIN)
unnamed: LED3.2 (DOUT), LED4.4 (DIN)
unnamed: LED4.2 (DOUT), LED5.4 (DIN)
unnamed: LED5.2 (DOUT), LED6.4 (DIN)
unnamed: LED7.2 (DOUT), LED8.4 (DIN)
unnamed: LED8.2 (DOUT), LED9.4 (DIN)
unnamed: LED9.2 (DOUT), LED10.4 (DIN)
unnamed: LED10.2 (DOUT), LED11.4 (DIN)
unnamed: LED11.2 (DOUT), LED12.4 (DIN)
unnamed: LED12.2 (DOUT), LED18.4 (DIN)
unnamed: LED13.4 (DIN), LED14.2 (DOUT)
unnamed: LED13.2 (DOUT), LED19.4 (DIN)
unnamed: LED14.4 (DIN), LED15.2 (DOUT)
unnamed: LED15.4 (DIN), LED16.2 (DOUT)
unnamed: LED16.4 (DIN), LED17.2 (DOUT)
unnamed: LED17.4 (DIN), LED18.2 (DOUT)
unnamed: LED19.2 (DOUT), LED20.4 (DIN)
unnamed: LED20.2 (DOUT), LED21.4 (DIN)
unnamed: LED21.2 (DOUT), LED22.4 (DIN)
unnamed: LED22.2 (DOUT), LED23.4 (DIN)
unnamed: LED23.2 (DOUT), LED24.4 (DIN)
unnamed: LED24.2 (DOUT), LED30.4 (DIN)
unnamed: LED25.4 (DIN), LED26.2 (DOUT)
unnamed: LED25.2 (DOUT), LED31.4 (DIN)
unnamed: LED26.4 (DIN), LED27.2 (DOUT)
unnamed: LED27.4 (DIN), LED28.2 (DOUT)
unnamed: LED28.4 (DIN), LED29.2 (DOUT)
unnamed: LED29.4 (DIN), LED30.2 (DOUT)
unnamed: LED31.2 (DOUT), LED32.4 (DIN)
unnamed: LED32.2 (DOUT), LED33.4 (DIN)
unnamed: LED33.2 (DOUT), LED34.4 (DIN)
unnamed: LED34.2 (DOUT), LED35.4 (DIN)
RESET: RES1.1, RES2.1, U1.22 (RST)
RGB_LINK: LED35.2 (DOUT)
SCL: P1.3 (SCL), U1.6 (3/PD0)
SDA: P1.4 (SDA), U1.5 (2/PD1)
VCC: J1.T, JP2.1, JP5.1, JP6.1, P1.2 (VCC), U1.21 (VCC), U2.5 (VP)
col0: SW6.1, SW12.1, SW18.1, SW24.1, SW30.S2, U1.16 (15/PB1)
col1: SW5.1, SW11.1, SW17.1, SW23.1, SW29.1, U1.14 (16/PB2)
col2: SW4.1, SW10.1, SW16.1, SW22.1, SW28.1, U1.15 (14/PB3)
col3: SW3.1, SW9.1, SW15.1, SW21.1, SW27.1, U1.13 (10/PB6)
col4: SW2.1, SW8.1, SW14.1, SW20.1, SW26.1, U1.17 (A0/PF7)
row0: D1.1 (K), D2.1 (K), D3.1 (K), D4.1 (K), D5.1 (K), D6.1 (K), U1.7 (4/PD4)
row1: D7.1 (K), D8.1 (K), D9.1 (K), D10.1 (K), D11.1 (K), D12.1 (K), U1.8 (5/PC6)
row2: D13.1 (K), D14.1 (K), D15.1 (K), D16.1 (K), D17.1 (K), D18.1 (K), U1.9 (6/PD7)
row3: D19.1 (K), D20.1 (K), D21.1 (K), D22.1 (K), D23.1 (K), D24.1 (K), U1.10 (7/PE6)
row4: D25.1 (K), D26.1 (K), D27.1 (K), D28.1 (K), D29.1 (K), D30.1 (K), U1.11 (8/PB4)

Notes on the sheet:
VCC/High = Left GND/Low = Right

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

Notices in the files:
Lotus 58 Classic/v1.28/Lotus58_Glow_128.kicad_pcb:
Licensed under Creative Commons BY-SA 4.0 International
Lotus 58 Glow/RP-C/Lotus58_RP-C.kicad_pcb:
Licensed under CERN-OHL-S v2 or any superseding version
